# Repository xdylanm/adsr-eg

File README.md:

# ADSR Envelope Generator

An envelope generator modeled on the 555-based ADSR originally proposed by Jonathan Jacky. It's worth looking through the evolution of this design - see documentation.

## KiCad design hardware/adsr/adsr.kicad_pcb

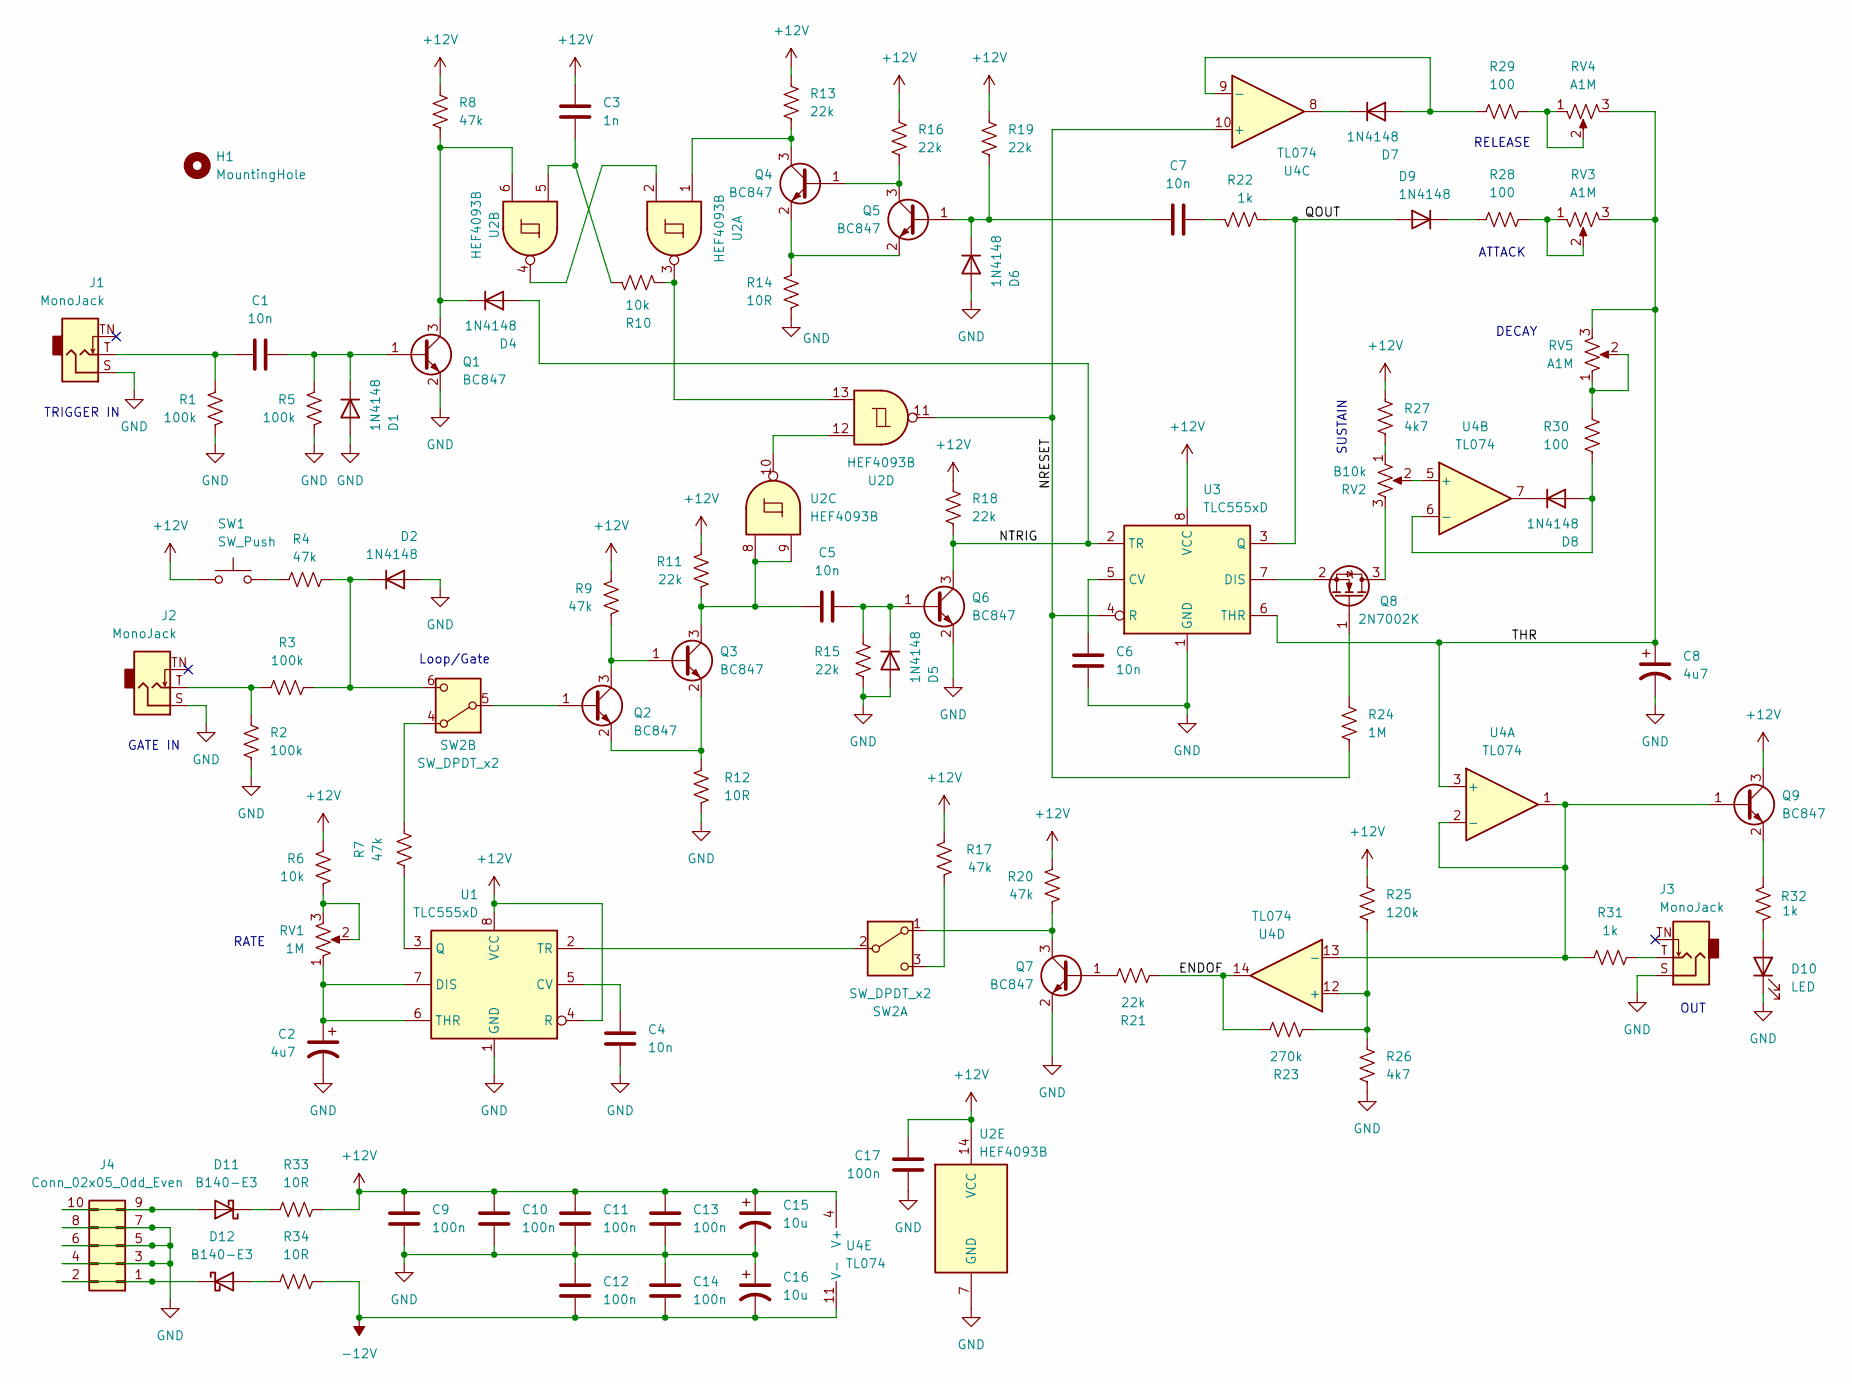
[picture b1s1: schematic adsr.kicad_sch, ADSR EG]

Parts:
C1, C4, C5, C6, C7: 10n; C_0805_2012Metric_Pad1.18x1.45mm_HandSolder
C2, C8: 4u7; CP_EIA-3216-18_Kemet-A_HandSolder
C3: 1n; C_0805_2012Metric_Pad1.18x1.45mm_HandSolder
C9, C10, C11, C12, C13, C14, C17: 100n; C_0805_2012Metric_Pad1.18x1.45mm_HandSolder
C15, C16: 10u; CP_Radial_D5.0mm_P2.50mm
D1, D2, D4, D5, D6, D7, D8, D9: 1N4148; D_SOD-123
D10: LED; LED_D3.0mm
D11, D12: B140-E3; D_SMA
H1: MountingHole; MountingHole_3.2mm_M3_DIN965
J1, J2, J3: MonoJack; Jack_3.5mm_QingPu_WQP-PJ301M-12_Vertical
J4: Conn_02x05_Odd_Even; IDC-Header_2x05_P2.54mm_Vertical
Q1, Q2, Q3, Q4, Q5, Q6, Q7, Q9: BC847; SOT-23
Q8: 2N7002K; SOT-23
R1, R2, R3, R5: 100k; R_0805_2012Metric_Pad1.20x1.40mm_HandSolder
R4, R7, R8, R9, R17, R20: 47k; R_0805_2012Metric_Pad1.20x1.40mm_HandSolder
R6, R10: 10k; R_0805_2012Metric_Pad1.20x1.40mm_HandSolder
R11, R13, R15, R16, R18, R19, R21: 22k; R_0805_2012Metric_Pad1.20x1.40mm_HandSolder
R12, R14, R33, R34: 10R; R_0805_2012Metric_Pad1.20x1.40mm_HandSolder
R22, R31, R32: 1k; R_0805_2012Metric_Pad1.20x1.40mm_HandSolder
R23: 270k; R_0805_2012Metric_Pad1.20x1.40mm_HandSolder
R24: 1M; R_0805_2012Metric_Pad1.20x1.40mm_HandSolder
R25: 120k; R_0805_2012Metric_Pad1.20x1.40mm_HandSolder
R26, R27: 4k7; R_0805_2012Metric_Pad1.20x1.40mm_HandSolder
R28, R29, R30: 100; R_0805_2012Metric_Pad1.20x1.40mm_HandSolder
RV1: 1M; Potentiometer_Bourns_PTV09A-1_Single_Vertical_thin
RV2: B10k; Potentiometer_Bourns_PTV09A-1_Single_Vertical_thin
RV3, RV4, RV5: A1M; Potentiometer_Bourns_PTV09A-1_Single_Vertical_thin
SW1: SW_Push; SW_PUSH_6mm
SW2: SW_DPDT_x2; SW_Dailywell_DPDT_2MD1T1B1M1
U1, U3: TLC555xD; SOIC-8_3.9x4.9mm_P1.27mm
U2: HEF4093B; SOIC-14_3.9x8.7mm_P1.27mm
U4: TL074; SOIC-14_3.9x8.7mm_P1.27mm

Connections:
+12V: C3.2, C9.2, C10.2, C11.2, C13.2, C15.1, C17.2, Q9.3 (C), R6.1, R8.2, R9.2, R11.1, R13.1, R16.1, R17.1, R18.1, R19.1, R20.1, R25.2, R27.1, R33.2, SW1.2, U1.4 (R), U1.8 (VCC), U2.14 (VCC), U3.8 (VCC), U4.4 (V+)
-12V: C12.1, C14.1, C16.2, R34.2, U4.11 (V-)
/ENDOF: R21.2, R23.2, U4.14
/NRESET: R24.2, U2.11, U3.4 (R), U4.10 (+)
/NTRIG: D4.2 (A), Q6.3 (C), R18.2, U3.2 (TR)
/QOUT: D9.2 (A), R22.2, U3.3 (Q)
/THR: C8.1, RV3.3, RV4.3, RV5.3, U3.6 (THR), U4.3 (+)
GND: C2.2, C4.1, C6.1, C8.2, C9.1, C10.1, C11.1, C12.2, C13.1, C14.2, C15.2, C16.1, C17.1, D1.2 (A), D2.2 (A), D5.2 (A), D6.2 (A), D10.1 (K), J1.S, J2.S, J3.S, J4.3, J4.4, J4.5, J4.6, J4.7, J4.8, Q1.2 (E), Q6.2 (E), Q7.2 (E), R1.1, R2.1, R5.1, R12.2, R14.1, R15.2, R26.1, U1.1 (GND), U2.7 (GND), U3.1 (GND)
unnamed: C1.2, J1.T, R1.2
unnamed: C3.1, R10.2, U2.5
unnamed: C7.1, R22.1
unnamed: C1.1, D1.1 (K), Q1.1 (B), R5.2
unnamed: D2.1 (K), R3.2, R4.1, SW2.6 (C)
unnamed: D4.1 (K), Q1.3 (C), R8.1, U2.6
unnamed: C5.1, D5.1 (K), Q6.1 (B), R15.1
unnamed: C7.2, D6.1 (K), Q5.1 (B), R19.2
unnamed: D7.2 (A), R29.1, U4.9 (-)
unnamed: D7.1 (K), U4.8
unnamed: D8.2 (A), R30.1, U4.6 (-)
unnamed: D8.1 (K), U4.7
unnamed: D9.1 (K), R28.1
unnamed: D10.2 (A), R32.1
unnamed: D11.2 (A), J4.9, J4.10
unnamed: D11.1 (K), R33.1
unnamed: D12.2 (A), R34.1
unnamed: D12.1 (K), J4.1, J4.2
unnamed: J2.T, R2.2, R3.1
unnamed: J3.T, R31.2
unnamed: Q2.1 (B), SW2.5 (B)
unnamed: Q2.3 (C), Q3.1 (B), R9.1
unnamed: Q2.2 (E), Q3.2 (E), R12.1
unnamed: C5.2, Q3.3 (C), R11.2, U2.8, U2.9
unnamed: Q4.1 (B), Q5.3 (C), R16.2
unnamed: Q4.3 (C), R13.2, U2.1
unnamed: Q4.2 (E), Q5.2 (E), R14.2
unnamed: Q7.1 (B), R21.1
unnamed: Q7.3 (C), R20.2, SW2.1 (A)
unnamed: Q8.3 (D), RV2.3
unnamed: Q8.1 (G), R24.1
unnamed: Q8.2 (S), U3.7 (DIS)
unnamed: Q9.1 (B), R31.1, U4.1, U4.2 (-), U4.13 (-)
unnamed: Q9.2 (E), R32.2
unnamed: R4.2, SW1.1
unnamed: R6.2, RV1.2, RV1.3
unnamed: R10.1, U2.3, U2.13
unnamed: R27.2, RV2.1
unnamed: R28.2, RV3.1, RV3.2
unnamed: R29.2, RV4.1, RV4.2
unnamed: R30.2, RV5.1, RV5.2
unnamed: SW2.2 (B), U1.2 (TR)
unnamed: R17.2, SW2.3 (C)
unnamed: R7.1, SW2.4 (A)
unnamed: C4.2, U1.5 (CV)
unnamed: C2.1, RV1.1, U1.6 (THR), U1.7 (DIS)
unnamed: R7.2, U1.3 (Q)
unnamed: U2.2, U2.4
unnamed: U2.10, U2.12
unnamed: C6.2, U3.5 (CV)
unnamed: RV2.2, U4.5 (+)
unnamed: R23.1, R25.1, R26.2, U4.12 (+)

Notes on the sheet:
OUT
Loop/Gate
ATTACK
GATE IN
RELEASE
RATE
SUSTAIN
TRIGGER IN
DECAY

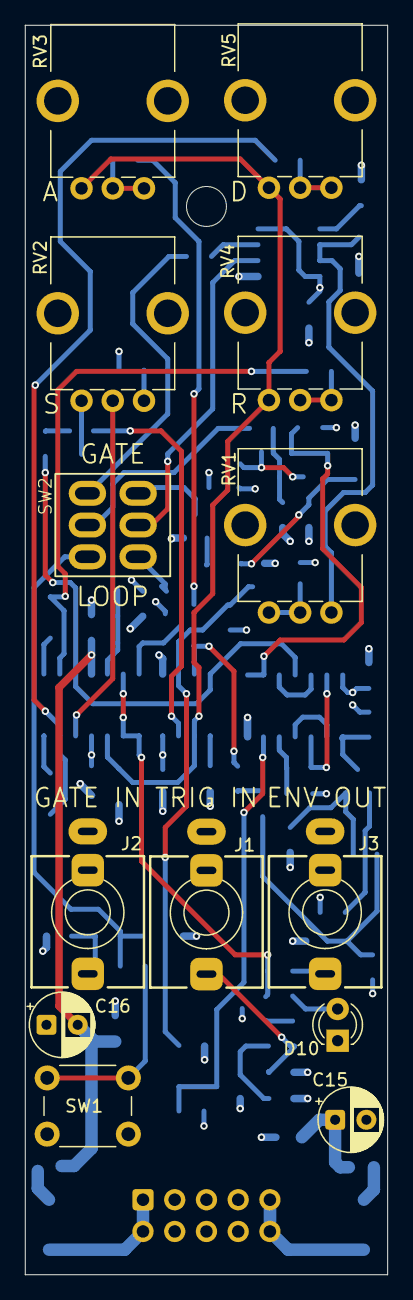
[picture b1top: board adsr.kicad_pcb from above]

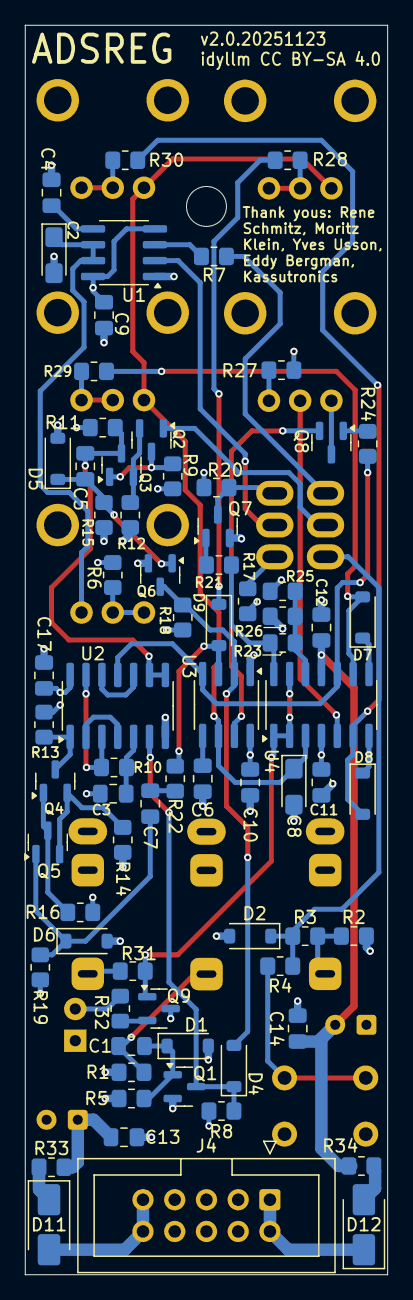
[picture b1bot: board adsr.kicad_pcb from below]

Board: 4 copper layers, 29.0 x 100.0 mm, 87 parts (73 on the bottom side), 60 nets.

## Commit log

2025-07-07 renaming .md to .rst
2025-09-16 Initial firmware for single chanel gate delay implemented for ATTiny13a
2025-09-16 Cleaning up tests and readme for gate delay firmware
2025-09-16 Put debug LED code behind an ifdef, changed timing to 8ms-2s range
2025-09-18 v1 dual gate delay PCB
2025-09-18 Updating documentation and notes
2025-09-28 Initial hardware design for ADSR EG, verified on breadboard.
2025-09-28 Moved gate delay to a separate repo, removing from ADSR
2025-09-28 Moved gate delay firmware to a separate repository, removing from ADSR
2025-09-28 Updated documentation. Moved README back to .rst, removed gate delay documents (moved to an independent repository), added some frontmatter
2025-09-28 Cleaning up images (moved to gate delay repository)
2025-09-29 Documentation cleanup
2025-09-29 Added missing gate R on MOSFET
2025-09-30 added mechanical hole and final silk cleanup
2025-10-19 Conversion to mkdocs/material for documentation
2025-10-20 Docs cleanup, added block diagram
2025-10-21 Updated block diagram
2025-10-21 Migrate to mkdocs/material (#1)
    * Conversion to mkdocs/material for documentation
    * Added block diagram
2025-11-08 Committing WIP on ADSR with trigger: Falstad circuit & schematic, some changes to the KiCAD schematic (incomplete)
2025-11-11 Build and validation for the v1.0 PCB
2025-11-11 Build and validation notes for the v1.0 PCB
2025-11-13 V1 build (#2)
    Build and validation notes for the v1.0 PCB
2025-11-21 schematic built and tested on breadboard
2025-11-21 added schematic screenshot from Falstad and updated the simulation circuit (link)
2025-11-21 routed PCB, needs cleanup
2025-11-21 routing cleanup
2025-11-24 clean up silk, check board, generate gerbers for v2
2025-11-26 Updated documentation for trigger input
2025-12-16 Added missing bom.csv (changed gitignore) and block diagram update
2025-12-16 Updated BOM
2025-12-21 Updated assembly guide after assembling and testing two boards. Added annotations to schematic.
2025-12-24 Faceplate with art. Tested with 3DP and printouts. Adjustments marked on layout.
2025-12-24 Updating docs, fixing minor issues.
2025-12-27 Clean up and regenerate schematic.pdf (out of date before)
2025-12-27 Feat/external trigger (#3)
    * Committing WIP on ADSR with trigger: Falstad circuit & schematic, some changes to the KiCAD schematic
    * schematic built and tested on breadboard
    * added schematic screenshot from Falstad and updated the simulation circuit (link)
    * routed PCB, needs cleanup
    * routing cleanup
    * clean up silk, check board, generate gerbers for v2
2025-12-27 Redrawing the schematic to show how the trigger could be added as an extension. Not implemented/tested.

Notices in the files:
hardware/adsr/adsr.kicad_pcb:
CC BY-SA 4.0
idyllm CC BY-SA 4.0
